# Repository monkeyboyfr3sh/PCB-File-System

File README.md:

# PCB-File-System
This will be a test setup for EAGLE file control

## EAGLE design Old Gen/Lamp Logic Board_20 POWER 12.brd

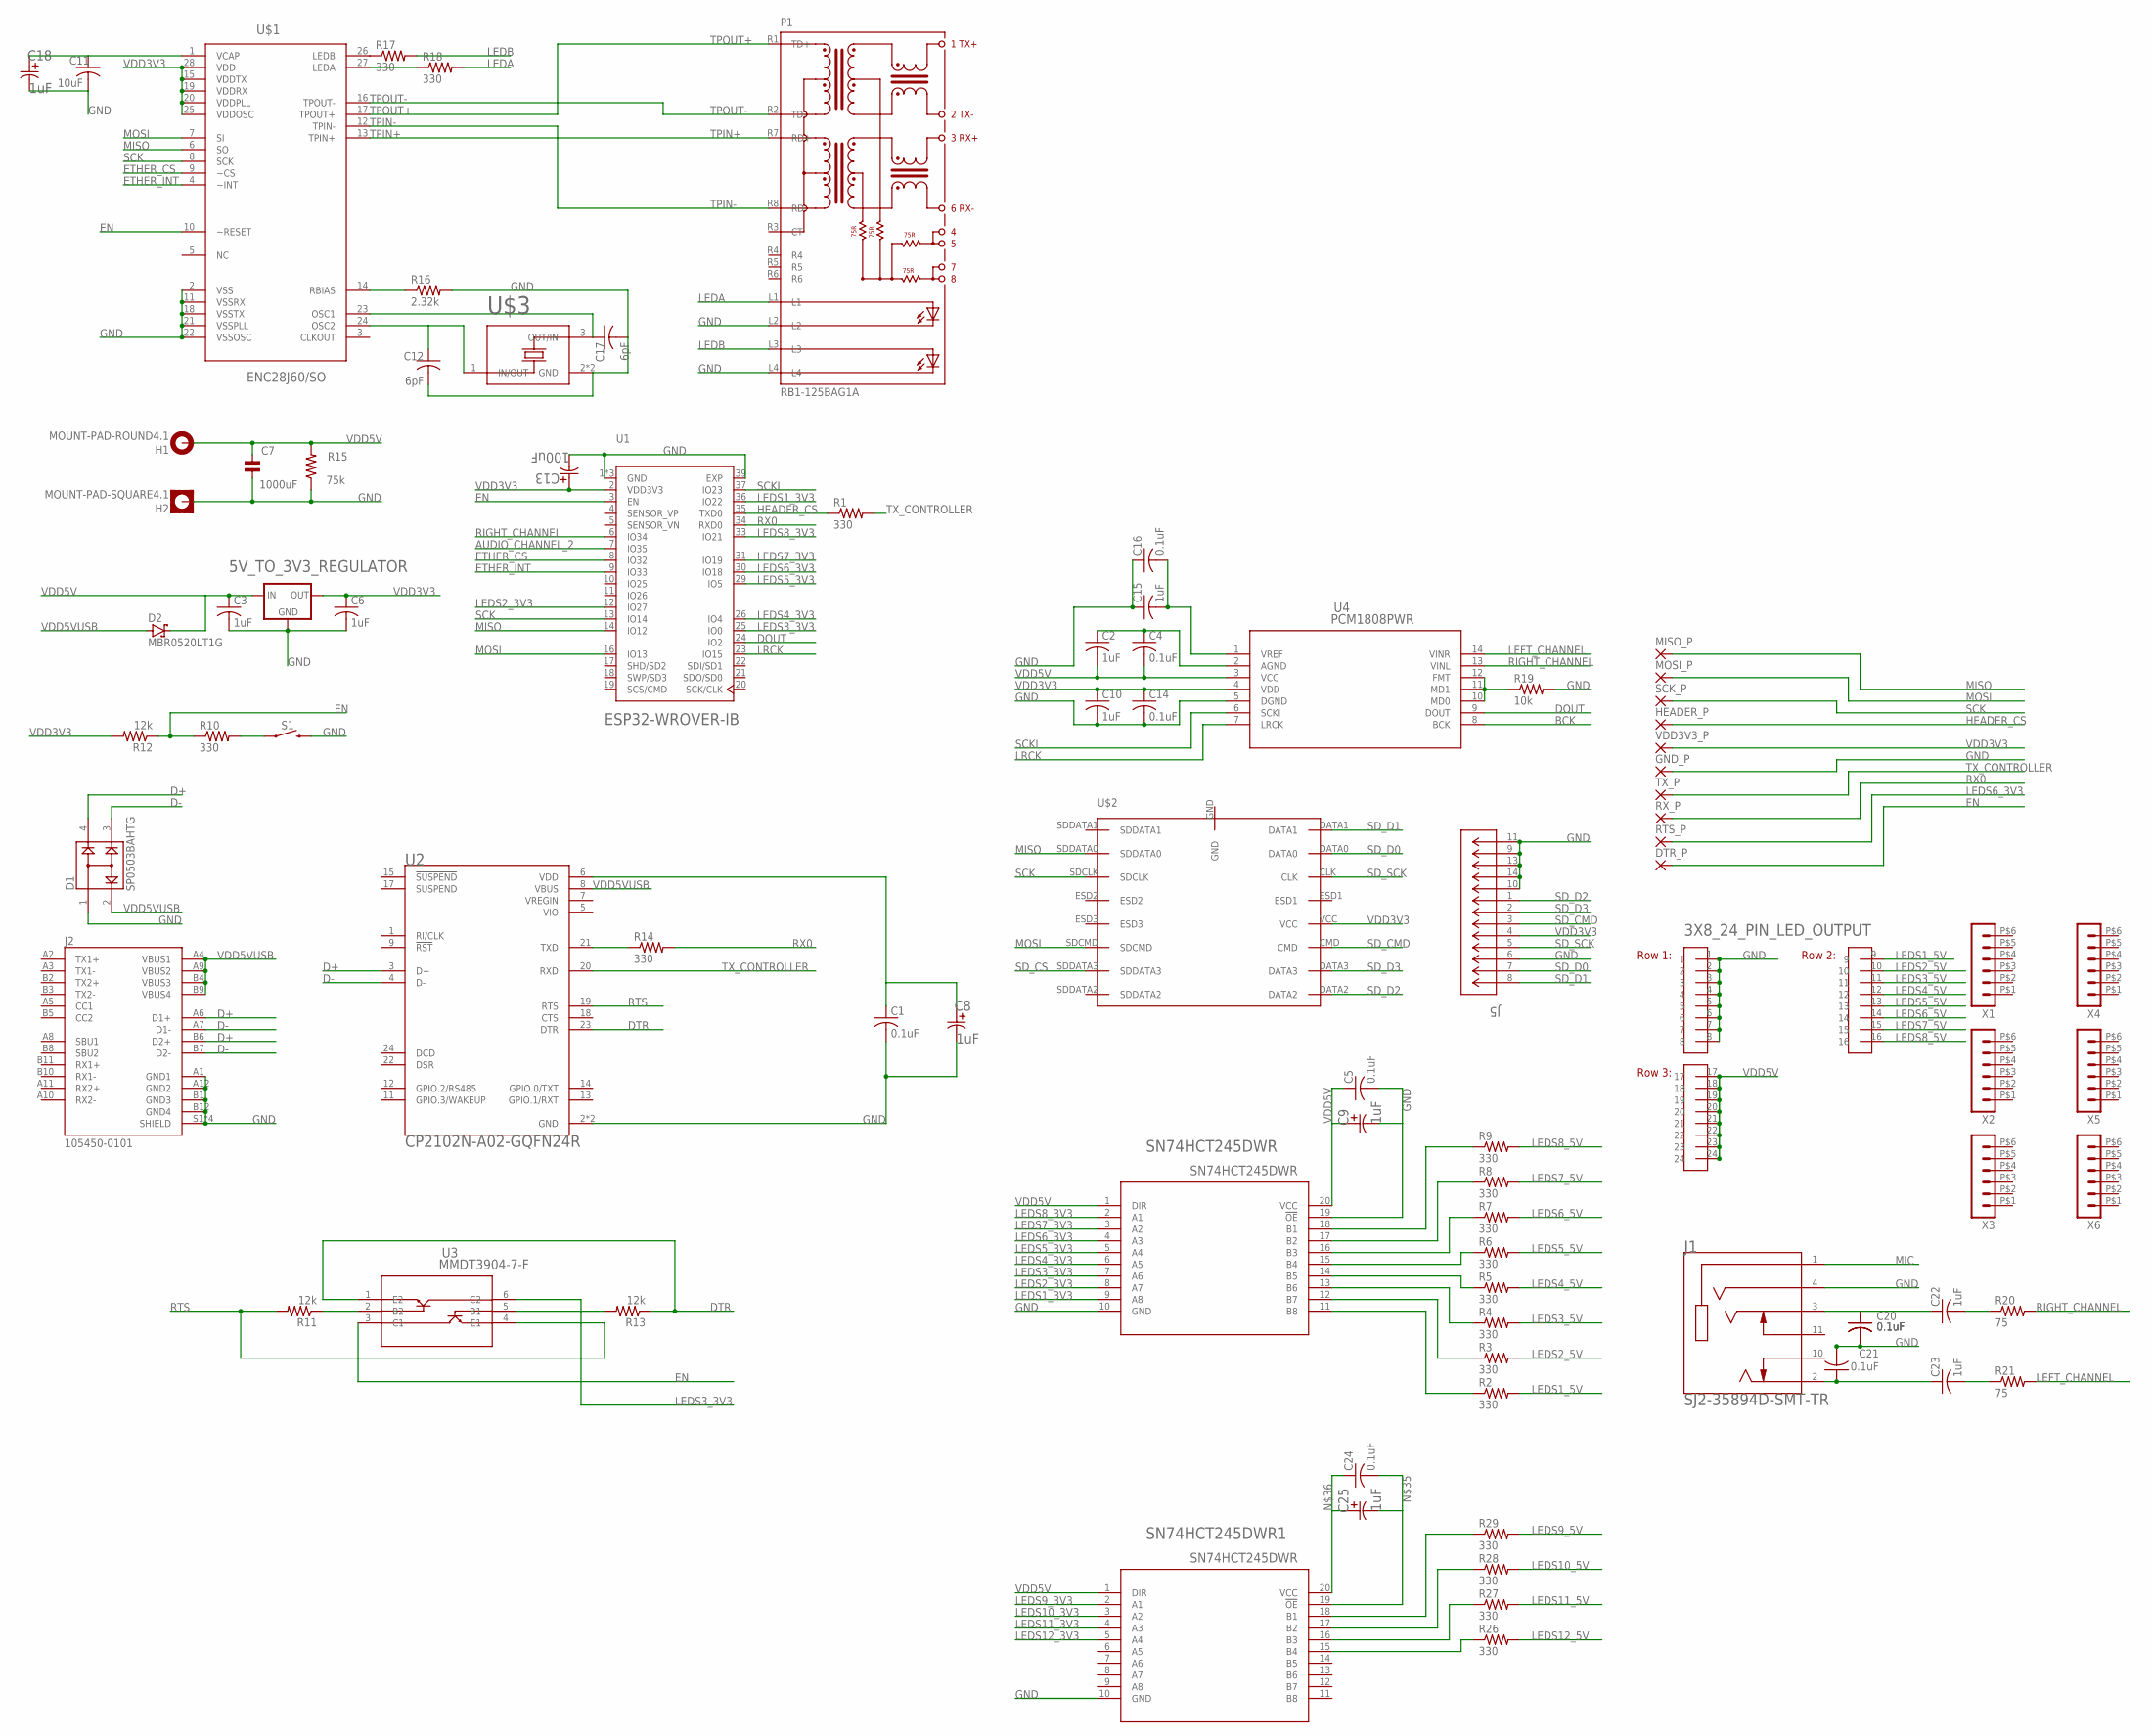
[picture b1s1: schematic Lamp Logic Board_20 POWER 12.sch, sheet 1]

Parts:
3X8_24_PIN_LED_OUTPUT: 3X8PINHEAD
5V_TO_3V3_REGULATOR: LM1117MP-1.8; SOT223
C1, C4, C14, C16: 0.1uF; C0402
C2, C3, C6, C10, C15, C22, C23: 1uF; C0402
C5, C19, C20, C21, C24: 0.1uF; C0805
C7: 1000uF; ENP2,0-5
C8, C9, C18, C25: 1uF; CAP_EEFC_B
C11: 10uF; C0402
C12, C17: 6pF; C0402
C13: 100uF; CAP_EEFC_B
D1: SP0503BAHTG; SOT143
D2: MBR0520LT1G; SOD-123
DTR_P: SMD2; SMD1,27-2,54
GND_P: SMD2; SMD1,27-2,54
H1: MOUNT-PAD-ROUND4.1; 4,1-PAD
H2: MOUNT-PAD-SQUARE4.1; 4,1-PAD-SQUARE
HEADER_P: SMD2; SMD1,27-2,54
J1: SJ2-35894D-SMT-TR; CUI_SJ2-35894D-SMT-TR
J2: 105450-0101; MOLEX_105450-0101
J5: LLC; CON00218_8
MISO_P: SMD2; SMD1,27-2,54
MOSI_P: SMD2; SMD1,27-2,54
P1: RB1-125BAG1A; WIZNET_RB1-125BAG1A
R1, R2, R3, R4, R5, R6, R7, R8, R9, R10, R14, R17, R18, R26, R27, R28, R29: 330; R1206
R11, R12, R13: 12k; R1206
R15: 75k; 0309/12
R16: 2.32k; R1206
R19: 10k; R1206
R20, R21: 75; R1206
RTS_P: SMD2; SMD1,27-2,54
RX_P: SMD2; SMD1,27-2,54
S1: MOMENTARY-SWITCH-SPST-SMD-6.0X3.5MM; TACTILE_SWITCH_SMD_6.0X3.5MM
SCK_P: SMD2; SMD1,27-2,54
SN74HCT245DWR, SN74HCT245DWR1: SN74HCT245DWR; DW20
TX_P: SMD2; SMD1,27-2,54
U1: ESP32-WROVER-IB; XCVR_ESP32-WROVER-I
U2: CP2102N-A02-GQFN24R; SILABS_CP2102N-A02-GQFN24R
U3: MMDT3904-7-F; SOT-363
U4: PCM1808PWR; PW14
U$1: ENC28J60/SO; SOIC127P1034X264-28N
U$2: CM1624-08DE
U$3: ECS-250-10-37B-CTN-TR
VDD3V3_P: SMD2; SMD1,27-2,54
X1, X2, X3, X4, X5, X6: HEADER_POS6_43045-0600; 43045-0600

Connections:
AUDIO_CHANNEL_2: U1.7 (IO35)
BCK: U4.8 (BCK)
D+: D1.4, J2.A6 (D1+), J2.B6 (D2+), U2.3 (D+)
D-: D1.3, J2.A7 (D1-), J2.B7 (D2-), U2.4 (D-)
DOUT: U1.24 (IO2), U4.9 (DOUT)
DTR: R13.1, U2.23 (DTR), U3.1 (E2)
EN: DTR_P.1, R10.1, R12.1, U1.3 (EN), U3.3 (C1), U$1.10 (~RESET)
ETHER_CS: U1.8 (IO32), U$1.9 (~CS)
ETHER_INT: U1.9 (IO33), U$1.4 (~INT)
GND: 3X8_24_PIN_LED_OUTPUT.1, 3X8_24_PIN_LED_OUTPUT.2, 3X8_24_PIN_LED_OUTPUT.3, 3X8_24_PIN_LED_OUTPUT.4, 3X8_24_PIN_LED_OUTPUT.5, 3X8_24_PIN_LED_OUTPUT.6, 3X8_24_PIN_LED_OUTPUT.7, 3X8_24_PIN_LED_OUTPUT.8, 5V_TO_3V3_REGULATOR.1 (GND), C1.2, C3.2, C5.2, C6.2, C7.1, C8.2, C9.2, C10.2, C11.2, C12.2, C13.2, C14.2, C15.1, C16.1, C17.2, C18.2, C19.2, C20.2, C21.2, D1.1, GND_P.1, H2.B4,1, J1.4 (RING2), J2.A1 (GND1), J2.A12 (GND2), J2.B1 (GND3), J2.B12 (GND4), J2.S1 (SHIELD), J2.S2 (SHIELD), J2.S3 (SHIELD), J2.S4 (SHIELD), J5.6, J5.9, J5.10, J5.11, J5.13, J5.14, P1.L2, P1.L4, R15.1, R16.2, R19.2, S1.2, SN74HCT245DWR.10 (GND), SN74HCT245DWR.19 (!OE), SN74HCT245DWR1.10 (GND), U1.1 (GND), U1.15 (GND), U1.38 (GND), U1.39 (EXP), U2.2 (GND), U2.25 (GND), U4.5 (DGND), U$1.2 (VSS), U$1.11 (VSSRX), U$1.18 (VSSTX), U$1.21 (VSSPLL), U$1.22 (VSSOSC), U$3.2 (GND), U$3.4 (GND)
HEADER_CS: HEADER_P.1, R1.1, U1.35 (TXD0)
LEDA: P1.L1, R18.2
LEDB: P1.L3, R17.2
LEDS1_3V3: SN74HCT245DWR.9 (A8), U1.36 (IO22)
LEDS1_5V: 3X8_24_PIN_LED_OUTPUT.9, R2.2
LEDS2_3V3: SN74HCT245DWR.8 (A7), U1.12 (IO27)
LEDS2_5V: 3X8_24_PIN_LED_OUTPUT.10, R3.2
LEDS3_3V3: SN74HCT245DWR.7 (A6), U1.25 (IO0), U3.6 (C2)
LEDS3_5V: 3X8_24_PIN_LED_OUTPUT.11, R4.2
LEDS4_3V3: SN74HCT245DWR.6 (A5), U1.26 (IO4)
LEDS4_5V: 3X8_24_PIN_LED_OUTPUT.12, R5.2
LEDS5_3V3: SN74HCT245DWR.5 (A4), U1.29 (IO5)
LEDS5_5V: 3X8_24_PIN_LED_OUTPUT.13, R6.2
LEDS6_3V3: RTS_P.1, SN74HCT245DWR.4 (A3), U1.30 (IO18)
LEDS6_5V: 3X8_24_PIN_LED_OUTPUT.14, R7.2
LEDS7_3V3: SN74HCT245DWR.3 (A2), U1.31 (IO19)
LEDS7_5V: 3X8_24_PIN_LED_OUTPUT.15, R8.2
LEDS8_3V3: SN74HCT245DWR.2 (A1), U1.33 (IO21)
LEDS8_5V: 3X8_24_PIN_LED_OUTPUT.16, R9.2
LEDS9_3V3: SN74HCT245DWR1.2 (A1)
LEDS9_5V: R29.2
LEDS10_3V3: SN74HCT245DWR1.3 (A2)
LEDS10_5V: R28.2
LEDS11_3V3: SN74HCT245DWR1.4 (A3)
LEDS11_5V: R27.2
LEDS12_3V3: SN74HCT245DWR1.5 (A4)
LEDS12_5V: R26.2
LEFT_CHANNEL: R21.2, U4.14 (VINR)
LRCK: U1.23 (IO15), U4.7 (LRCK)
MIC: J1.1 (SLEEVE)
MISO: MISO_P.1, U1.14 (IO12), U$1.6 (SO), U$2.SDDATA0
MOSI: MOSI_P.1, U1.16 (IO13), U$1.7 (SI), U$2.SDCMD
unnamed: R9.1, SN74HCT245DWR.18 (B1)
unnamed: C2.1, C4.1, U4.2 (AGND)
unnamed: C22.1, J1.3 (RING1)
unnamed: C21.1, C23.1, J1.2 (TIP)
unnamed: C1.1, C8.1, U2.6 (VDD)
unnamed: R8.1, SN74HCT245DWR.17 (B2)
unnamed: R11.1, U3.2 (B2)
unnamed: R13.2, U3.5 (B1)
unnamed: R10.2, S1.1
unnamed: R7.1, SN74HCT245DWR.16 (B3)
unnamed: R6.1, SN74HCT245DWR.15 (B4)
unnamed: R5.1, SN74HCT245DWR.14 (B5)
unnamed: R4.1, SN74HCT245DWR.13 (B6)
unnamed: R3.1, SN74HCT245DWR.12 (B7)
unnamed: R2.1, SN74HCT245DWR.11 (B8)
unnamed: C22.2, R20.1
unnamed: C15.2, C16.2, U4.1 (VREF)
unnamed: R14.1, U2.21 (TXD)
unnamed: C11.1, C18.1, U$1.1 (VCAP)
unnamed: R16.1, U$1.14 (RBIAS)
unnamed: C12.1, U$1.24 (OSC2), U$3.1 (IN/OUT)
unnamed: C17.1, U$1.23 (OSC1), U$3.3 (OUT/IN)
unnamed: R17.1, U$1.26 (LEDB)
unnamed: C23.2, R21.1
unnamed: R18.1, U$1.27 (LEDA)
unnamed: R29.1, SN74HCT245DWR1.18 (B1)
unnamed: R28.1, SN74HCT245DWR1.17 (B2)
unnamed: R27.1, SN74HCT245DWR1.16 (B3)
unnamed: R26.1, SN74HCT245DWR1.15 (B4)
unnamed: R19.1, U4.10 (MD0), U4.11 (MD1), U4.12 (FMT)
unnamed: C24.2, C25.2, SN74HCT245DWR1.19 (!OE)
unnamed: C24.1, C25.1, SN74HCT245DWR1.20 (VCC)
RIGHT_CHANNEL: C19.1, C20.1, R20.2, U1.6 (IO34), U4.13 (VINL)
RTS: R11.2, U2.19 (RTS), U3.4 (E1)
RX0: R14.2, RX_P.1, U1.34 (RXD0)
SCK: SCK_P.1, U1.13 (IO14), U$1.8 (SCK), U$2.SDCLK
SCKI: U1.37 (IO23), U4.6 (SCKI)
SD_CMD: J5.3, U$2.CMD
SD_CS: U$2.SDDATA3
SD_D0: J5.7, U$2.DATA0
SD_D1: J5.8, U$2.DATA1
SD_D2: J5.1, U$2.DATA2
SD_D3: J5.2, U$2.DATA3
SD_SCK: J5.5, U$2.CLK
TPIN+: P1.R7 (RD+), U$1.13 (TPIN+)
TPIN-: P1.R8 (RD-), U$1.12 (TPIN-)
TPOUT+: P1.R1 (TD+), U$1.17 (TPOUT+)
TPOUT-: P1.R2 (TD-), U$1.16 (TPOUT-)
TX_CONTROLLER: R1.2, TX_P.1, U2.20 (RXD)
VDD3V3: 5V_TO_3V3_REGULATOR.2 (OUT), 5V_TO_3V3_REGULATOR.4 (OUT), C6.1, C10.1, C13.1, C14.1, J5.4, R12.2, U1.2 (VDD3V3), U4.4 (VDD), U$1.15 (VDDTX), U$1.19 (VDDRX), U$1.20 (VDDPLL), U$1.25 (VDDOSC), U$1.28 (VDD), U$2.VCC, VDD3V3_P.1
VDD5V: 3X8_24_PIN_LED_OUTPUT.17, 3X8_24_PIN_LED_OUTPUT.18, 3X8_24_PIN_LED_OUTPUT.19, 3X8_24_PIN_LED_OUTPUT.20, 3X8_24_PIN_LED_OUTPUT.21, 3X8_24_PIN_LED_OUTPUT.22, 3X8_24_PIN_LED_OUTPUT.23, 3X8_24_PIN_LED_OUTPUT.24, 5V_TO_3V3_REGULATOR.3 (IN), C2.2, C3.1, C4.2, C5.1, C7.2, C9.1, D2.C, H1.B4,1, R15.2, SN74HCT245DWR.1 (DIR), SN74HCT245DWR.20 (VCC), SN74HCT245DWR1.1 (DIR), U4.3 (VCC)
VDD5VUSB: D1.2, D2.A, J2.A4 (VBUS1), J2.A9 (VBUS2), J2.B4 (VBUS3), J2.B9 (VBUS4), U2.8 (VBUS)
VREGIN: U2.7 (VREGIN)

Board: 2 copper layers, 86 parts (0 on the bottom side), 82 nets, no tracks yet.

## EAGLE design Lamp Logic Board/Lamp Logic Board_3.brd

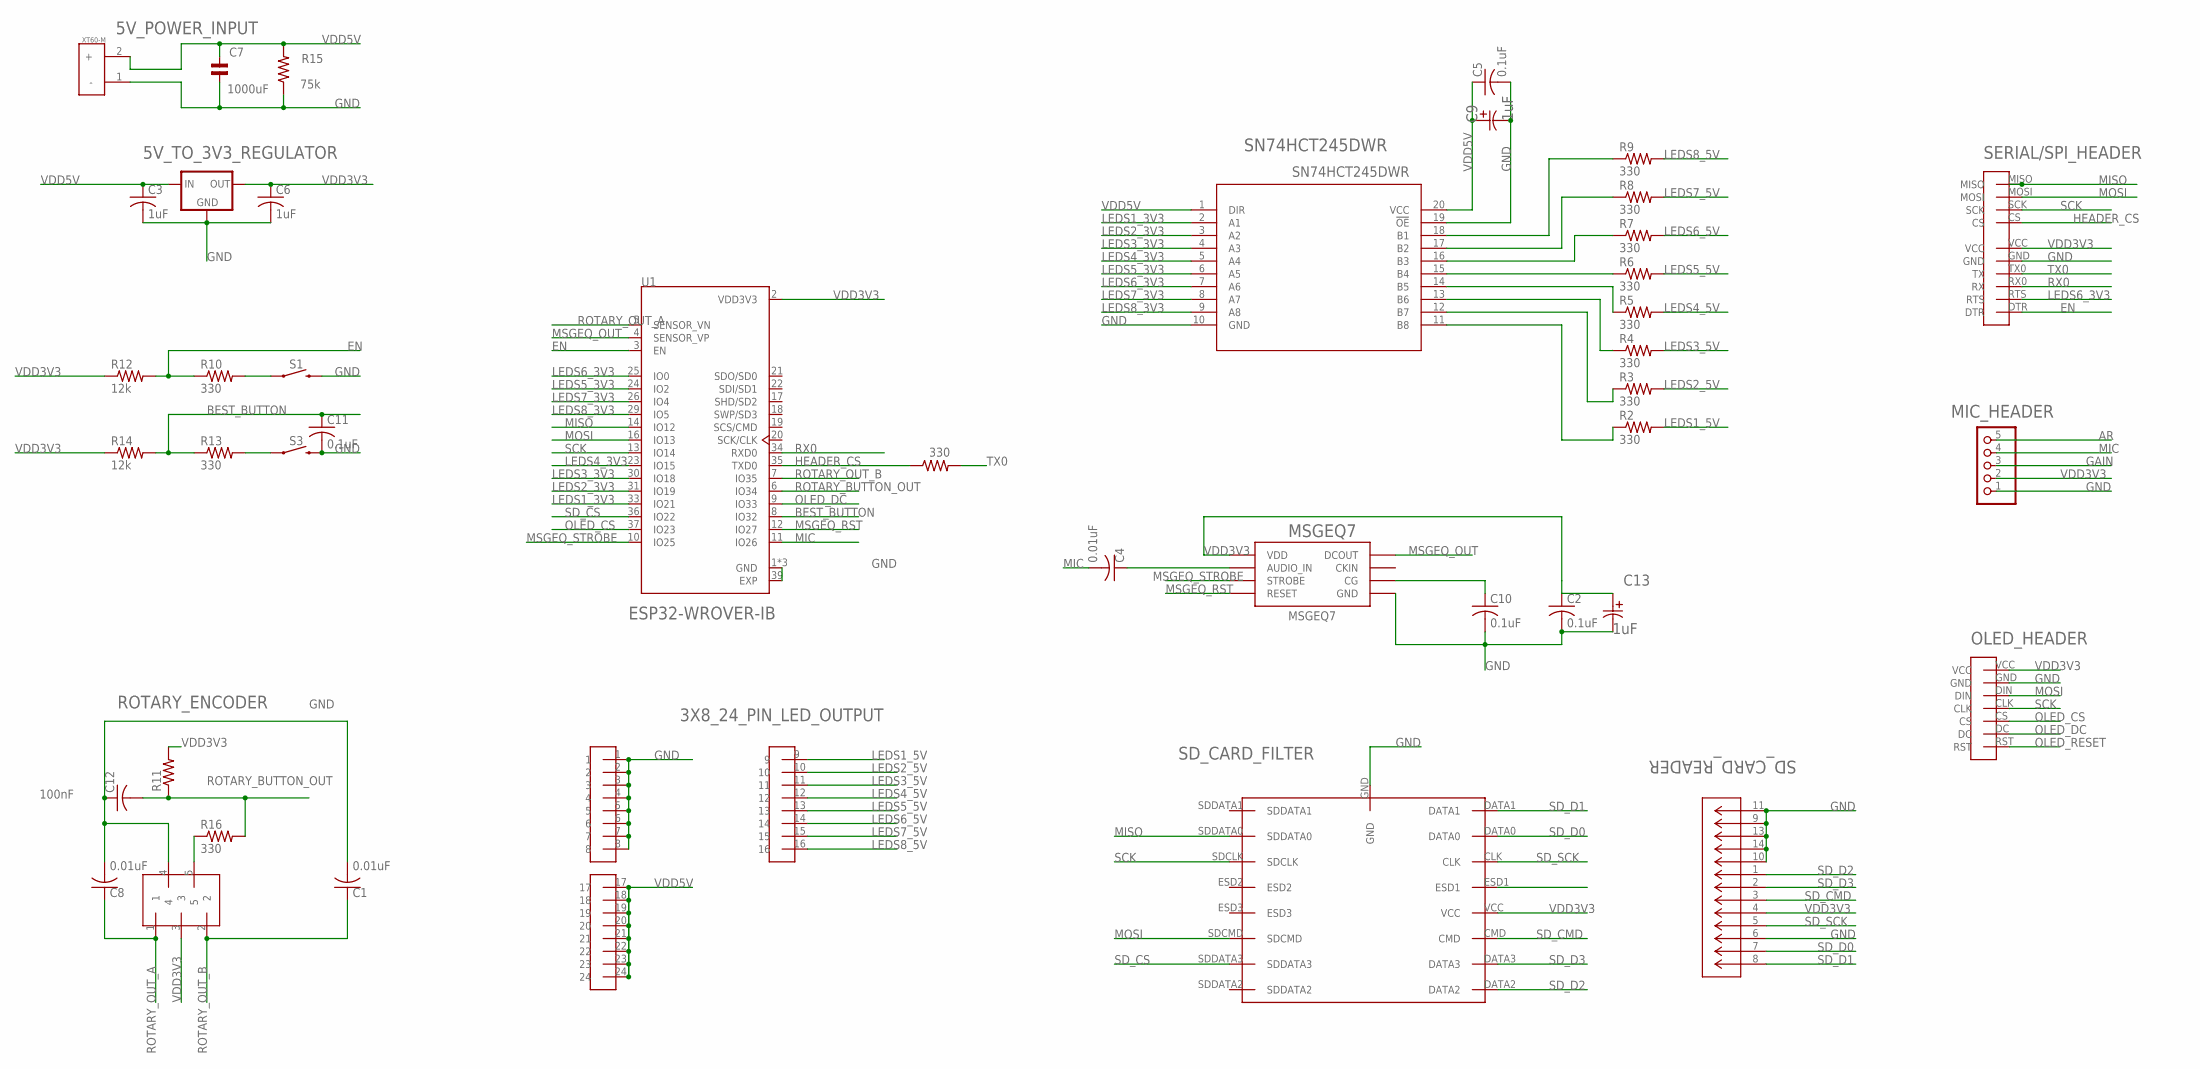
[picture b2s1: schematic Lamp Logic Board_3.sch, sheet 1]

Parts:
3X8_24_PIN_LED_OUTPUT: 3X8PINHEAD
5V_POWER_INPUT: XT60-M; AMASS_XT60-M
5V_TO_3V3_REGULATOR: LM1117MP-1.8; SOT223
C1, C4, C8: 0.01uF; C0402
C2, C5, C10, C11: 0.1uF; C0805
C3, C6: 1uF; C0402
C7: 1000uF; ENP2,0-5
C9, C13: 1uF; CAP_EEFC_B
C12: 100nF; C0402
MIC_HEADER: PINHD-1X5; 1X05
MSGEQ7: MSGEQ7DIL; DIL-08
OLED_HEADER: SPIOLED_STANDOFF; SPIOLED_STADOFF
R1, R2, R3, R4, R5, R6, R7, R8, R9, R10, R13, R16: 330; R1206
R11: R-US_R0603; R0603
R12, R14: 12k; R0603
R15: 75k; 0309/12
ROTARY_ENCODER: EN11-HSM1AF15; EN11-HSM
S1: MOMENTARY-SWITCH-SPST-SMD-6.0X3.5MM; TACTILE_SWITCH_SMD_6.0X3.5MM
S3: MOMENTARY-SWITCH-SPST-SMD-12MM; TACTILE_SWITCH_SMD_12MM
SD_CARD_FILTER: CM1624-08DE
SD_CARD_READER: LLC; CON00218_8
SERIAL/SPI_HEADER: 2X6PINHEAD
SN74HCT245DWR: SN74HCT245DWR; DW20
U1: ESP32-WROVER-IB; XCVR_ESP32-WROVER-I

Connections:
AR: MIC_HEADER.5
BEST_BUTTON: C11.1, R13.1, R14.2, U1.8 (IO32)
EN: R10.1, R12.2, SERIAL/SPI_HEADER.DTR, U1.3 (EN)
GAIN: MIC_HEADER.3
GND: 3X8_24_PIN_LED_OUTPUT.1, 3X8_24_PIN_LED_OUTPUT.2, 3X8_24_PIN_LED_OUTPUT.3, 3X8_24_PIN_LED_OUTPUT.4, 3X8_24_PIN_LED_OUTPUT.5, 3X8_24_PIN_LED_OUTPUT.6, 3X8_24_PIN_LED_OUTPUT.7, 3X8_24_PIN_LED_OUTPUT.8, 5V_POWER_INPUT.1 (-), 5V_TO_3V3_REGULATOR.1 (GND), C1.2, C2.2, C3.2, C5.2, C6.2, C7.1, C8.2, C9.2, C10.2, C11.2, C12.1, C13.2, MIC_HEADER.1, MSGEQ7.2 (GND), OLED_HEADER.GND, R15.1, ROTARY_ENCODER.4, S1.2, S3.3 (2), SD_CARD_FILTER.GND, SD_CARD_READER.6, SD_CARD_READER.9, SD_CARD_READER.10, SD_CARD_READER.11, SD_CARD_READER.13, SD_CARD_READER.14, SERIAL/SPI_HEADER.GND, SN74HCT245DWR.10 (GND), SN74HCT245DWR.19 (!OE), U1.1 (GND), U1.15 (GND), U1.38 (GND), U1.39 (EXP)
HEADER_CS: R1.1, SERIAL/SPI_HEADER.CS, U1.35 (TXD0)
LEDS1_3V3: SN74HCT245DWR.2 (A1), U1.33 (IO21)
LEDS1_5V: 3X8_24_PIN_LED_OUTPUT.9, R2.2
LEDS2_3V3: SN74HCT245DWR.3 (A2), U1.31 (IO19)
LEDS2_5V: 3X8_24_PIN_LED_OUTPUT.10, R3.2
LEDS3_3V3: SN74HCT245DWR.4 (A3), U1.30 (IO18)
LEDS3_5V: 3X8_24_PIN_LED_OUTPUT.11, R4.2
LEDS4_3V3: SN74HCT245DWR.5 (A4), U1.23 (IO15)
LEDS4_5V: 3X8_24_PIN_LED_OUTPUT.12, R5.2
LEDS5_3V3: SN74HCT245DWR.6 (A5), U1.24 (IO2)
LEDS5_5V: 3X8_24_PIN_LED_OUTPUT.13, R6.2
LEDS6_3V3: SERIAL/SPI_HEADER.RTS, SN74HCT245DWR.7 (A6), U1.25 (IO0)
LEDS6_5V: 3X8_24_PIN_LED_OUTPUT.14, R7.2
LEDS7_3V3: SN74HCT245DWR.8 (A7), U1.26 (IO4)
LEDS7_5V: 3X8_24_PIN_LED_OUTPUT.15, R8.2
LEDS8_3V3: SN74HCT245DWR.9 (A8), U1.29 (IO5)
LEDS8_5V: 3X8_24_PIN_LED_OUTPUT.16, R9.2
MIC: C4.2, MIC_HEADER.4, U1.11 (IO26)
MISO: SD_CARD_FILTER.SDDATA0, SERIAL/SPI_HEADER.MISO, U1.14 (IO12)
MOSI: OLED_HEADER.DIN, SD_CARD_FILTER.SDCMD, SERIAL/SPI_HEADER.MOSI, U1.16 (IO13)
MSGEQ_OUT: MSGEQ7.3 (DCOUT), U1.4 (SENSOR_VP)
MSGEQ_RST: MSGEQ7.7 (RESET), U1.12 (IO27)
MSGEQ_STROBE: MSGEQ7.4 (STROBE), U1.10 (IO25)
unnamed: R9.1, SN74HCT245DWR.18 (B1)
unnamed: C4.1, MSGEQ7.5 (AUDIO_IN)
unnamed: C10.1, MSGEQ7.6 (CG)
unnamed: R16.1, ROTARY_ENCODER.5
unnamed: R8.1, SN74HCT245DWR.17 (B2)
unnamed: R13.2, S3.1
unnamed: R10.2, S1.1
unnamed: R7.1, SN74HCT245DWR.16 (B3)
unnamed: R6.1, SN74HCT245DWR.15 (B4)
unnamed: R5.1, SN74HCT245DWR.14 (B5)
unnamed: R4.1, SN74HCT245DWR.13 (B6)
unnamed: R3.1, SN74HCT245DWR.12 (B7)
unnamed: R2.1, SN74HCT245DWR.11 (B8)
OLED_CS: OLED_HEADER.CS, U1.37 (IO23)
OLED_DC: OLED_HEADER.DC, U1.9 (IO33)
OLED_RESET: OLED_HEADER.RST
ROTARY_BUTTON_OUT: C12.2, R11.1, R16.2, U1.6 (IO34)
ROTARY_OUT_A: C8.1, ROTARY_ENCODER.1, U1.5 (SENSOR_VN)
ROTARY_OUT_B: C1.1, ROTARY_ENCODER.2, U1.7 (IO35)
RX0: SERIAL/SPI_HEADER.RX0 (RX), U1.34 (RXD0)
SCK: OLED_HEADER.CLK, SD_CARD_FILTER.SDCLK, SERIAL/SPI_HEADER.SCK, U1.13 (IO14)
SD_CMD: SD_CARD_FILTER.CMD, SD_CARD_READER.3
SD_CS: SD_CARD_FILTER.SDDATA3, U1.36 (IO22)
SD_D0: SD_CARD_FILTER.DATA0, SD_CARD_READER.7
SD_D1: SD_CARD_FILTER.DATA1, SD_CARD_READER.8
SD_D2: SD_CARD_FILTER.DATA2, SD_CARD_READER.1
SD_D3: SD_CARD_FILTER.DATA3, SD_CARD_READER.2
SD_SCK: SD_CARD_FILTER.CLK, SD_CARD_READER.5
TX0: R1.2, SERIAL/SPI_HEADER.TX0 (TX)
VDD3V3: 5V_TO_3V3_REGULATOR.2 (OUT), 5V_TO_3V3_REGULATOR.4 (OUT), C2.1, C6.1, C13.1, MIC_HEADER.2, MSGEQ7.1 (VDD), OLED_HEADER.VCC, R11.2, R12.1, R14.1, ROTARY_ENCODER.3, SD_CARD_FILTER.VCC, SD_CARD_READER.4, SERIAL/SPI_HEADER.VCC, U1.2 (VDD3V3)
VDD5V: 3X8_24_PIN_LED_OUTPUT.17, 3X8_24_PIN_LED_OUTPUT.18, 3X8_24_PIN_LED_OUTPUT.19, 3X8_24_PIN_LED_OUTPUT.20, 3X8_24_PIN_LED_OUTPUT.21, 3X8_24_PIN_LED_OUTPUT.22, 3X8_24_PIN_LED_OUTPUT.23, 3X8_24_PIN_LED_OUTPUT.24, 5V_POWER_INPUT.2 (+), 5V_TO_3V3_REGULATOR.3 (IN), C3.1, C5.1, C7.2, C9.1, R15.2, SN74HCT245DWR.1 (DIR), SN74HCT245DWR.20 (VCC)

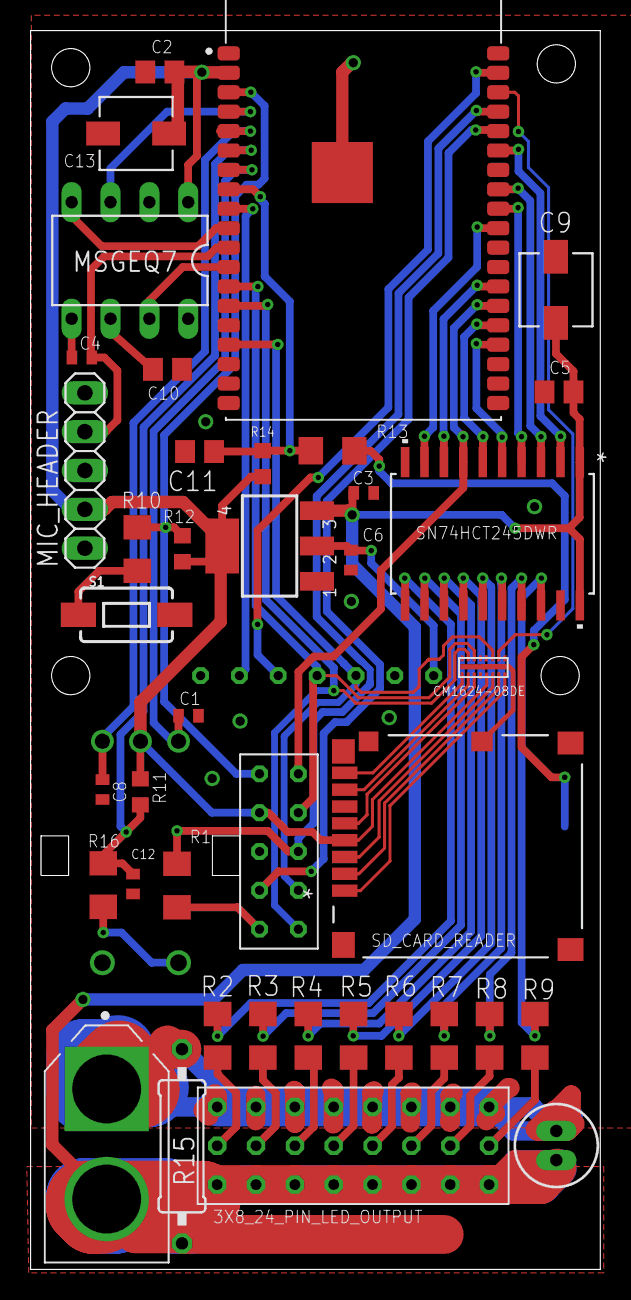
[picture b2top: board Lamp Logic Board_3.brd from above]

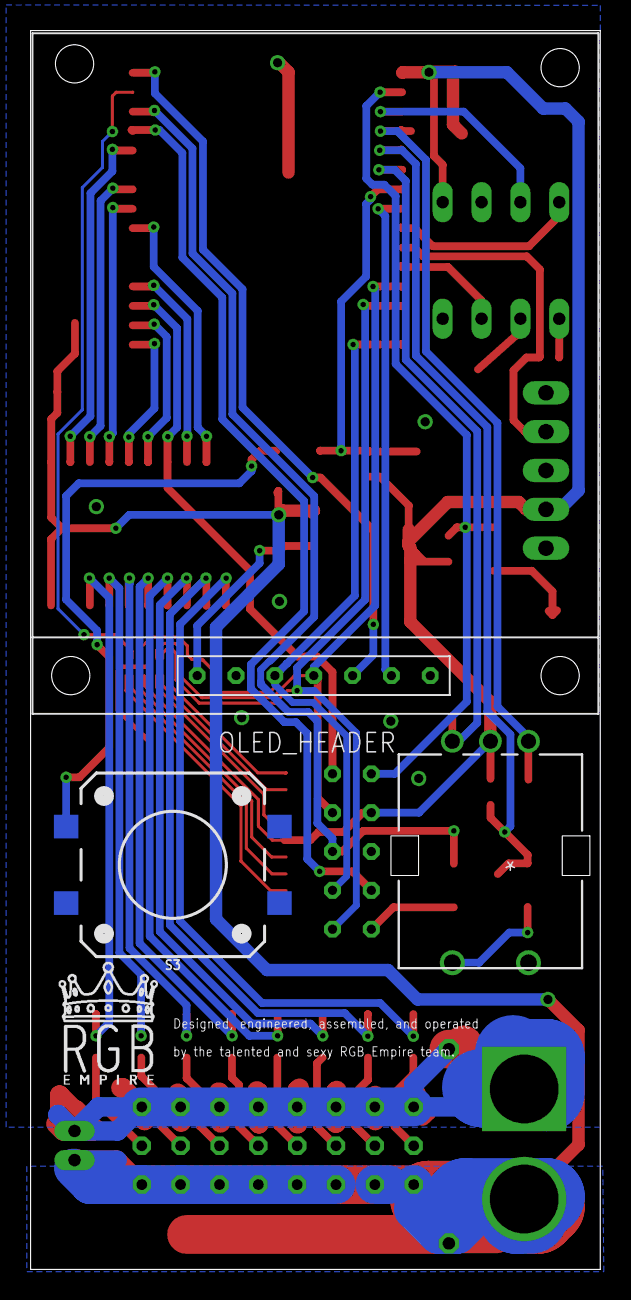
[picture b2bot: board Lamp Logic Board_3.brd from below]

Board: 2 copper layers, 37.2 x 81.0 mm, 43 parts (3 on the bottom side), 56 nets.

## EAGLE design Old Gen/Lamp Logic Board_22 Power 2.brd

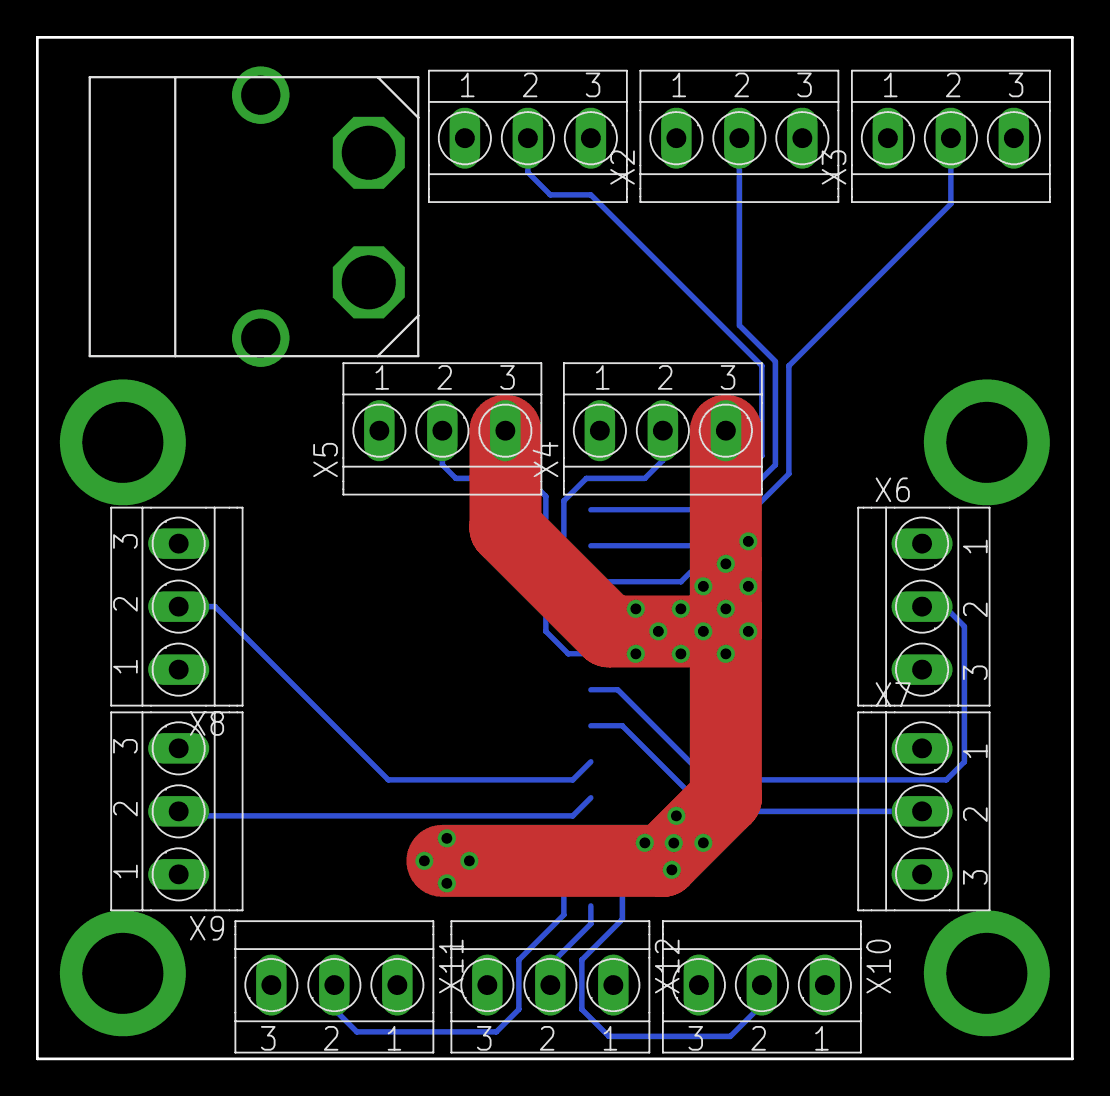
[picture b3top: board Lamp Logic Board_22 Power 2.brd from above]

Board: 2 copper layers, 57.5 x 56.8 mm, 15 parts (1 on the bottom side), 15 nets.

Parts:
U$1: POWERBOARD_TEMPLATEPOWERBOARD_TEMPLATE; 4,PIECE
U$2: MY_HEADER
U$3: XT60
X1, X2, X3, X4, X5, X6, X7, X8, X9, X10, X11, X12: TERMINAL-BLOCK-3.5MM-3-PIN-LONG-PAD; TERMINAL-BLOCK-3-PIN-3.5MM-LONG-PAD

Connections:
GND: U$1.P$1, U$1.P$2, U$1.P$3, U$1.P$4, U$2.P$13, U$2.P$14, U$2.P$21, U$2.P$22, U$3.-, U$3.-_HOLE, X1.3, X2.3, X3.3, X4.3, X5.3, X6.3, X7.3, X8.3, X9.3, X10.3, X11.3, X12.3
LEDS1_5V: U$2.P$12, X1.2
LEDS2_5V: U$2.P$11, X2.2
LEDS3_5V: U$2.P$10, X3.2
LEDS4_5V: U$2.P$9, X4.2
LEDS5_5V: U$2.P$8, X5.2
LEDS6_5V: U$2.P$7, X6.2
LEDS7_5V: U$2.P$6, X7.2
LEDS8_5V: U$2.P$5, X8.2
LEDS9_5V: U$2.P$4, X9.2
LEDS10_5V: U$2.P$3, X10.2
LEDS11_5V: U$2.P$2, X11.2
LEDS12_5V: U$2.P$1, X12.2
VDD3V3: U$2.P$19, U$2.P$20
VDD5V: U$2.P$23, U$2.P$24, U$3.+, U$3.+_HOLE, X1.1, X2.1, X3.1, X4.1, X5.1, X6.1, X7.1, X8.1, X9.1, X10.1, X11.1, X12.1

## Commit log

2019-12-13 Beginning of a new world
    Starting test
2019-12-13 Adding a new file
2020-01-17 Clearing it out
2020-01-17 PISS:Proper Implementation of Structure Setup
2020-02-09 Organizing library, starting new ark board.
2020-02-09 Adding esp32 and other stuff
2020-02-09 Removing big stuff

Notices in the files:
parts and their libraries:
cap-pan40: Copyright (C) 2004, Bob Starr
SparkFun-Switches: Licensing: Creative Commons ShareAlike 4.0 International - https://creativecommons.org/licenses/by-sa/4.0
lm1117: (c) 2014 Samuel Lourenço
